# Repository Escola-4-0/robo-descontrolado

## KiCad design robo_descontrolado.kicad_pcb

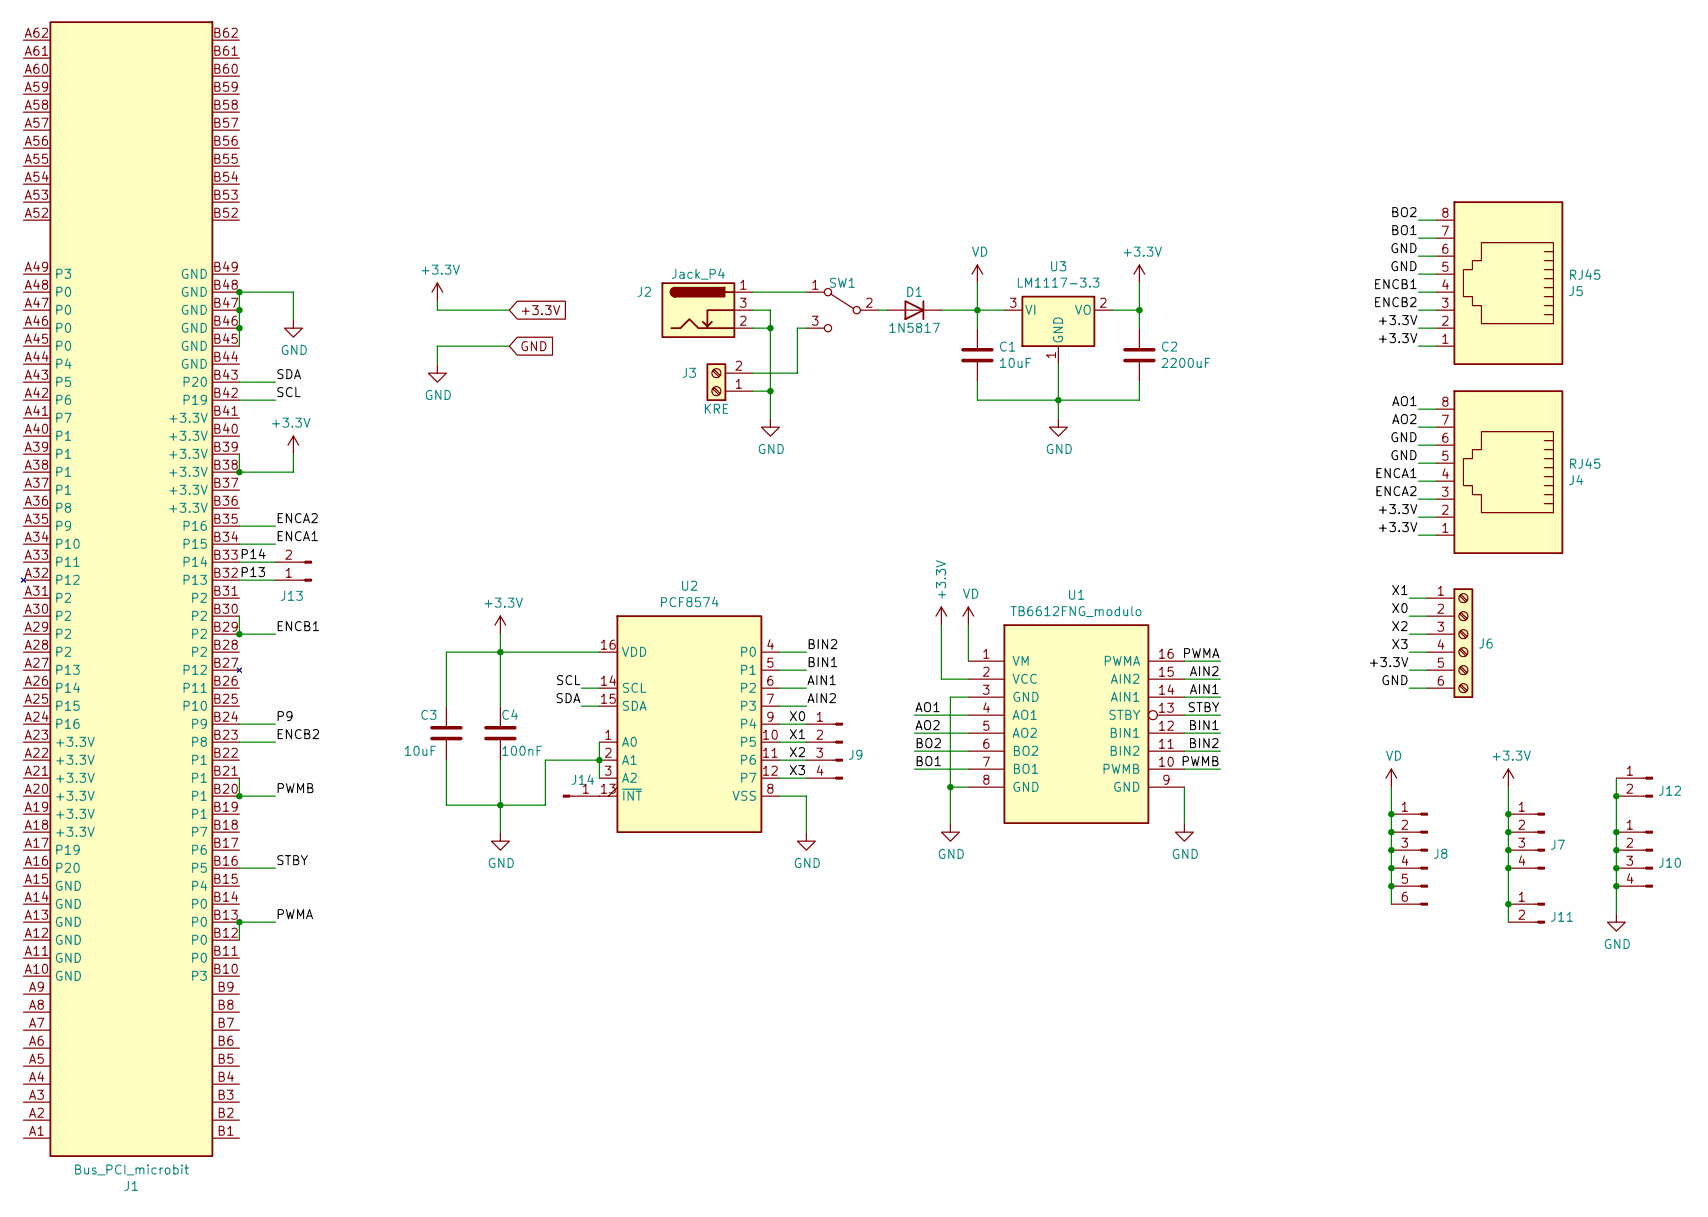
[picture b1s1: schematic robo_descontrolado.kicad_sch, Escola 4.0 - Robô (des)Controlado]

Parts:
C1, C3: 10uF; C_Radial_D5.0mm_H11.0mm_P2.00mm
C2: 2200uF; C_Radial_D10.0mm_H16.0mm_P5.00mm
C4: 100nF; C_Disc_D5.0mm_W2.5mm_P2.50mm
D1: 1N5817; D_A-405_P7.62mm_Horizontal
J1: Bus_PCI_microbit; pci_connector_microbit
J2: Jack_P4; BarrelJack_Horizontal
J3: KRE; TerminalBlock_bornier-2_P5.08mm
J4, J5: RJ45; RJ45_Amphenol_54602-x08_Horizontal
J6: Screw_Terminal_01x06; TerminalBlock_bornier-6_P5.08mm
J7, J9, J10: Conn_01x04_Male; PinHeader_1x04_P2.54mm_Vertical
J8: Conn_01x05_Male; PinHeader_2x03_P2.54mm_Vertical
J11, J12, J13: Conn_01x02_Male; PinHeader_1x02_P2.54mm_Vertical
J14: Conn_01x01_Male; PinHeader_1x01_P2.54mm_Vertical
SW1: SW_SPDT; Slide_Switch
U1: TB6612FNG_modulo
U2: PCF8574; DIP-16_W7.62mm_Socket
U3: LM1117-3.3; TO-220-3_Vertical

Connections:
+3.3V: C2.1, C3.1, C4.2, J1.B38 (+3.3V), J1.B39 (+3.3V), J4.1, J4.2, J5.1, J5.2, J6.5, J7.1, J7.2, J7.3, J7.4, J11.1, J11.2, U1.2 (VCC), U2.16 (VDD), U3.2 (VO)
/AIN1: U1.14 (AIN1), U2.6 (P2)
/AIN2: U1.15 (AIN2), U2.7 (P3)
/AO1: J4.8, U1.4 (AO1)
/AO2: J4.7, U1.5 (AO2)
/BIN1: U1.12 (BIN1), U2.5 (P1)
/BIN2: U1.11 (BIN2), U2.4 (P0)
/BO1: J5.7, U1.7 (BO1)
/BO2: J5.8, U1.6 (BO2)
/ENCA1: J1.B34 (P15), J4.4
/ENCA2: J1.B35 (P16), J4.3
/ENCB1: J1.B29 (P2), J1.B30 (P2), J5.4
/ENCB2: J1.B23 (P8), J5.3
/P9: J1.B24 (P9)
/P13: J1.B32 (P13), J13.1
/P14: J1.B33 (P14), J13.2
/PWMA: J1.B12 (P0), J1.B13 (P0), U1.16 (PWMA)
/PWMB: J1.B20 (P1), J1.B21 (P1), U1.10 (PWMB)
/SCL: J1.B42 (P19), U2.14 (SCL)
/SDA: J1.B43 (P20), U2.15 (SDA)
/STBY: J1.B16 (P5), U1.13 (STBY)
/X0: J6.2, J9.1, U2.9 (P4)
/X1: J6.1, J9.2, U2.10 (P5)
/X2: J6.3, J9.3, U2.11 (P6)
/X3: J6.4, J9.4, U2.12 (P7)
GND: C1.2, C2.2, C3.2, C4.1, J1.B45 (GND), J1.B46 (GND), J1.B47 (GND), J1.B48 (GND), J2.2, J2.3, J3.1, J4.5, J4.6, J5.5, J5.6, J6.6, J10.1, J10.2, J10.3, J10.4, J12.1, J12.2, U1.3 (GND), U1.8 (GND), U1.9 (GND), U2.1 (A0), U2.2 (A1), U2.3 (A2), U2.8 (VSS), U3.1 (GND)
unnamed: D1.2 (A), SW1.2 (B)
unnamed: J2.1, SW1.1 (A)
unnamed: J3.2, SW1.3 (C)
unnamed: J14.1, U2.13 (~INT)
VD: C1.1, D1.1 (K), J8.1, J8.2, J8.3, J8.4, J8.5, J8.6, U1.1 (VM), U3.3 (VI)

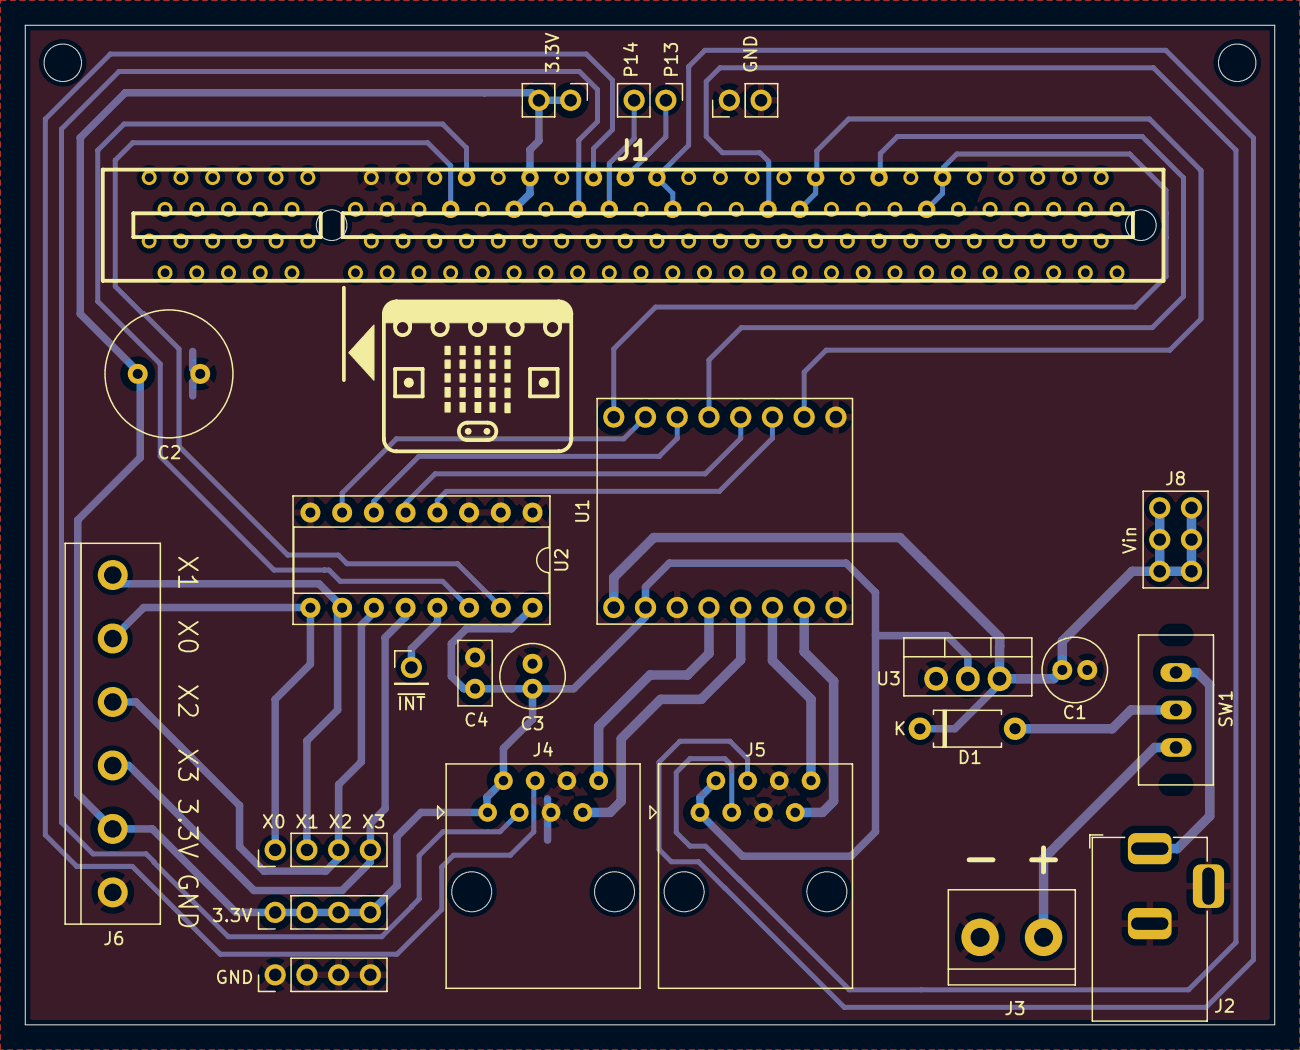
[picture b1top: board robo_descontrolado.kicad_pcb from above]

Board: 2 copper layers, 100.0 x 80.0 mm, 23 parts (0 on the bottom side), 30 nets.

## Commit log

2021-04-08 Adicionando Readme
2021-04-08 Adicionando a licença
2024-05-31 Nova versão com expansor i2c e IOs de propósito geral
2024-05-31 Corrige gitignore
